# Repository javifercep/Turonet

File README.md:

# Turonet

### Highlights ###

* SPI / I2C to USB bridge based on STM32F042X devices
* Developed with [KiCad](http://kicad-pcb.org/)

### Available software ###
This [repository](https://github.com/ingeniamc/serial-bridge) contains an example of USB to SPI bridge implementing the Motion Control Bus to interface Ingenia drives. 

The project is developed with [Atollic TrueSTUDIO](https://atollic.com/truestudio/)

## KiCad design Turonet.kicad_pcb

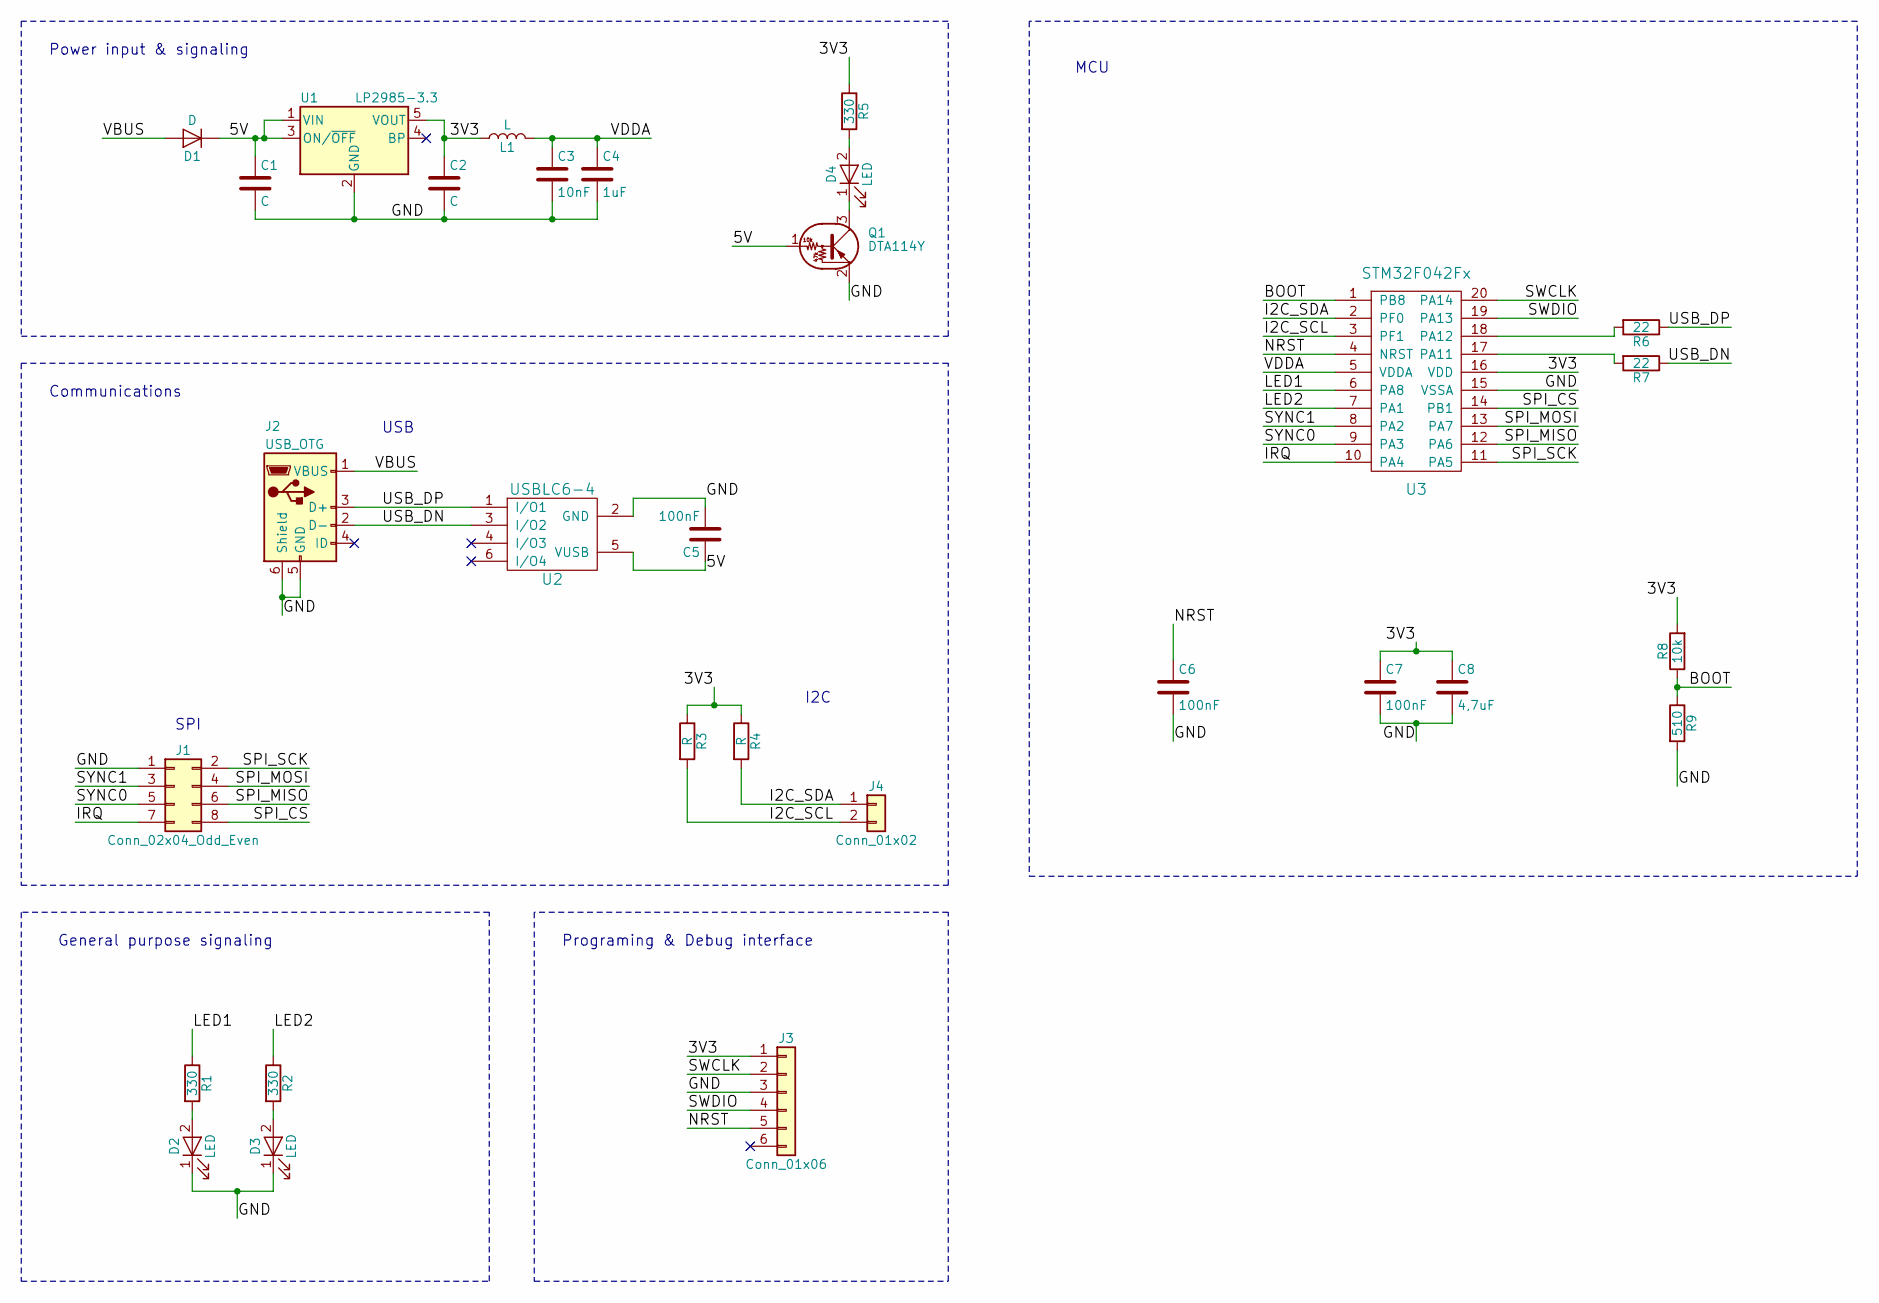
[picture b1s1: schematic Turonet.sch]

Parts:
C1, C2: C; C_0603_HandSoldering
C3: 10nF; C_0603_HandSoldering
C4: 1uF; C_0603_HandSoldering
C5, C6, C7: 100nF; C_0603_HandSoldering
C8: 4,7uF; C_0603_HandSoldering
D1: D; D_SOD-123
D2, D3, D4: LED; LED_0805_HandSoldering
J1: Conn_02x04_Odd_Even; Pin_Header_Angled_2x04_Pitch2.54mm
J2: USB_OTG; USB_Micro-B_Molex-105017-0001
J3: Conn_01x06; Pin_Header_Angled_1x06_Pitch2.54mm
J4: Conn_01x02; Pin_Header_Straight_1x02_Pitch2.54mm
L1: L; L_0603_HandSoldering
Q1: DTA114Y; SOT-23_Handsoldering
R1, R2, R5: 330; R_0603_HandSoldering
R3, R4: R; R_0603_HandSoldering
R6, R7: 22; R_0603_HandSoldering
R8: 10k; R_0603_HandSoldering
R9: 510; R_0603_HandSoldering
U1: LP2985-3.3; SOT-23-5_HandSoldering
U2: USBLC6-4; TSOT-23-6_HandSoldering
U3: STM32F042Fx; TSSOP-20_4.4x6.5mm_Pitch0.65mm

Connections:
/3V3: C2.1, C7.1, C8.1, J3.1, L1.1, R3.1, R4.1, R5.1, R8.2, U1.5 (VOUT), U3.16 (VDD)
/5V: C1.1, C5.1, D1.1 (K), Q1.1 (B), U1.1 (VIN), U1.3 (ON/~OFF~), U2.5 (VUSB)
/BOOT: R8.1, R9.1, U3.1 (PB8)
/GND: C1.2, C2.2, C3.2, C4.2, C5.2, C6.2, C7.2, C8.2, D2.1 (K), D3.1 (K), J1.1, J2.5 (GND), J2.6 (Shield), J3.3, Q1.2 (E), R9.2, U1.2 (GND), U2.2 (GND), U3.15 (VSSA)
/I2C_SCL: J4.2, R3.2, U3.3 (PF1)
/I2C_SDA: J4.1, R4.2, U3.2 (PF0)
/IRQ: J1.7, U3.10 (PA4)
/LED1: R1.1, U3.6 (PA8)
/LED2: R2.1, U3.7 (PA1)
/NRST: C6.1, J3.5, U3.4 (NRST)
/SPI_CS: J1.8, U3.14 (PB1)
/SPI_MISO: J1.6, U3.12 (PA6)
/SPI_MOSI: J1.4, U3.13 (PA7)
/SPI_SCK: J1.2, U3.11 (PA5)
/SWCLK: J3.2, U3.20 (PA14)
/SWDIO: J3.4, U3.19 (PA13)
/SYNC0: J1.5, U3.9 (PA3)
/SYNC1: J1.3, U3.8 (PA2)
/USB_DN: J2.2 (D-), R7.1, U2.3 (I/O2)
/USB_DP: J2.3 (D+), R6.1, U2.1 (I/O1)
/VBUS: D1.2 (A), J2.1 (VBUS)
/VDDA: C3.1, C4.1, L1.2, U3.5 (VDDA)
unnamed: D2.2 (A), R1.2
unnamed: D3.2 (A), R2.2
unnamed: D4.1 (K), Q1.3 (C)
unnamed: D4.2 (A), R5.2
unnamed: R6.2, U3.18 (PA12)
unnamed: R7.2, U3.17 (PA11)

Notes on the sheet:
Power input & signaling
Communications
USB
SPI
I2C
General purpose signaling
Programing & Debug interface
MCU

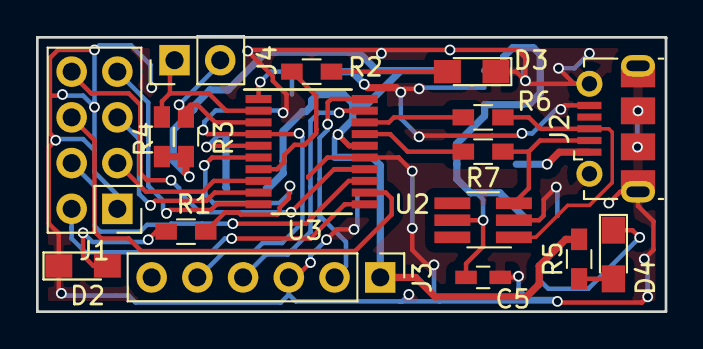
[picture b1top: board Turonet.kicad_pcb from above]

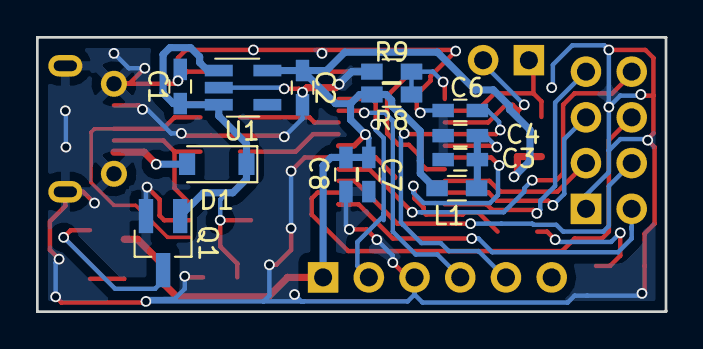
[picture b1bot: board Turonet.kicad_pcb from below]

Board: 2 copper layers, 34.9 x 15.2 mm, 30 parts (13 on the bottom side), 28 nets.

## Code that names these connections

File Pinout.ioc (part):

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Mcu.Name=STM32F042F4Px
Mcu.Package=TSSOP20
Mcu.UserName=STM32F042F4Px
PA0.Signal=S_TIM2_CH1_ETR
PA1.Signal=S_TIM2_CH2
PA11.Mode=Device
PA11.Signal=USB_DM
PA12.Mode=Device
PA12.Signal=USB_DP
PA13.Mode=Serial_Wire
PA13.Signal=SYS_SWDIO
PA14.Mode=Serial_Wire
PA14.Signal=SYS_SWCLK
PA2.Signal=GPIO_Input
PA3.Signal=GPIO_Input
PA4.Signal=GPIO_Output
PA5.Mode=Full_Duplex_Master
PA5.Signal=SPI1_SCK
PA6.Mode=Full_Duplex_Master
PA6.Signal=SPI1_MISO
PA7.Mode=Full_Duplex_Master
PA7.Signal=SPI1_MOSI
PB1.Signal=GPIO_Input
PB8.Signal=GPIO_Output
PF0-OSC_IN.Mode=I2C
PF0-OSC_IN.Signal=I2C1_SDA
PF1-OSC_OUT.Mode=I2C
PF1-OSC_OUT.Signal=I2C1_SCL
RCC.SYSCLKFreq_VALUE=48000000
RCC.SYSCLKSource=RCC_SYSCLKSOURCE_PLLCLK

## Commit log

2018-10-10 first release
